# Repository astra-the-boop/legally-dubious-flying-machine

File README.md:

# la legally dubious flying machine
### Might break several aerospace, telecom, and public order laws but we ball
## Project members: Astra (@astra.celestine on Slack), Ghost (@Minh Anh Ghost on Slack), MD (not in hc), Doggy (not in hc), bingle

## Basically, an RC plane based around just regular commercial airplanes.; ~1m in length; Arduino-controlled; Using LoRa for communication; might add autopilot; DIY Controller + software

---
## Dependencies and libraries or whatever:
-

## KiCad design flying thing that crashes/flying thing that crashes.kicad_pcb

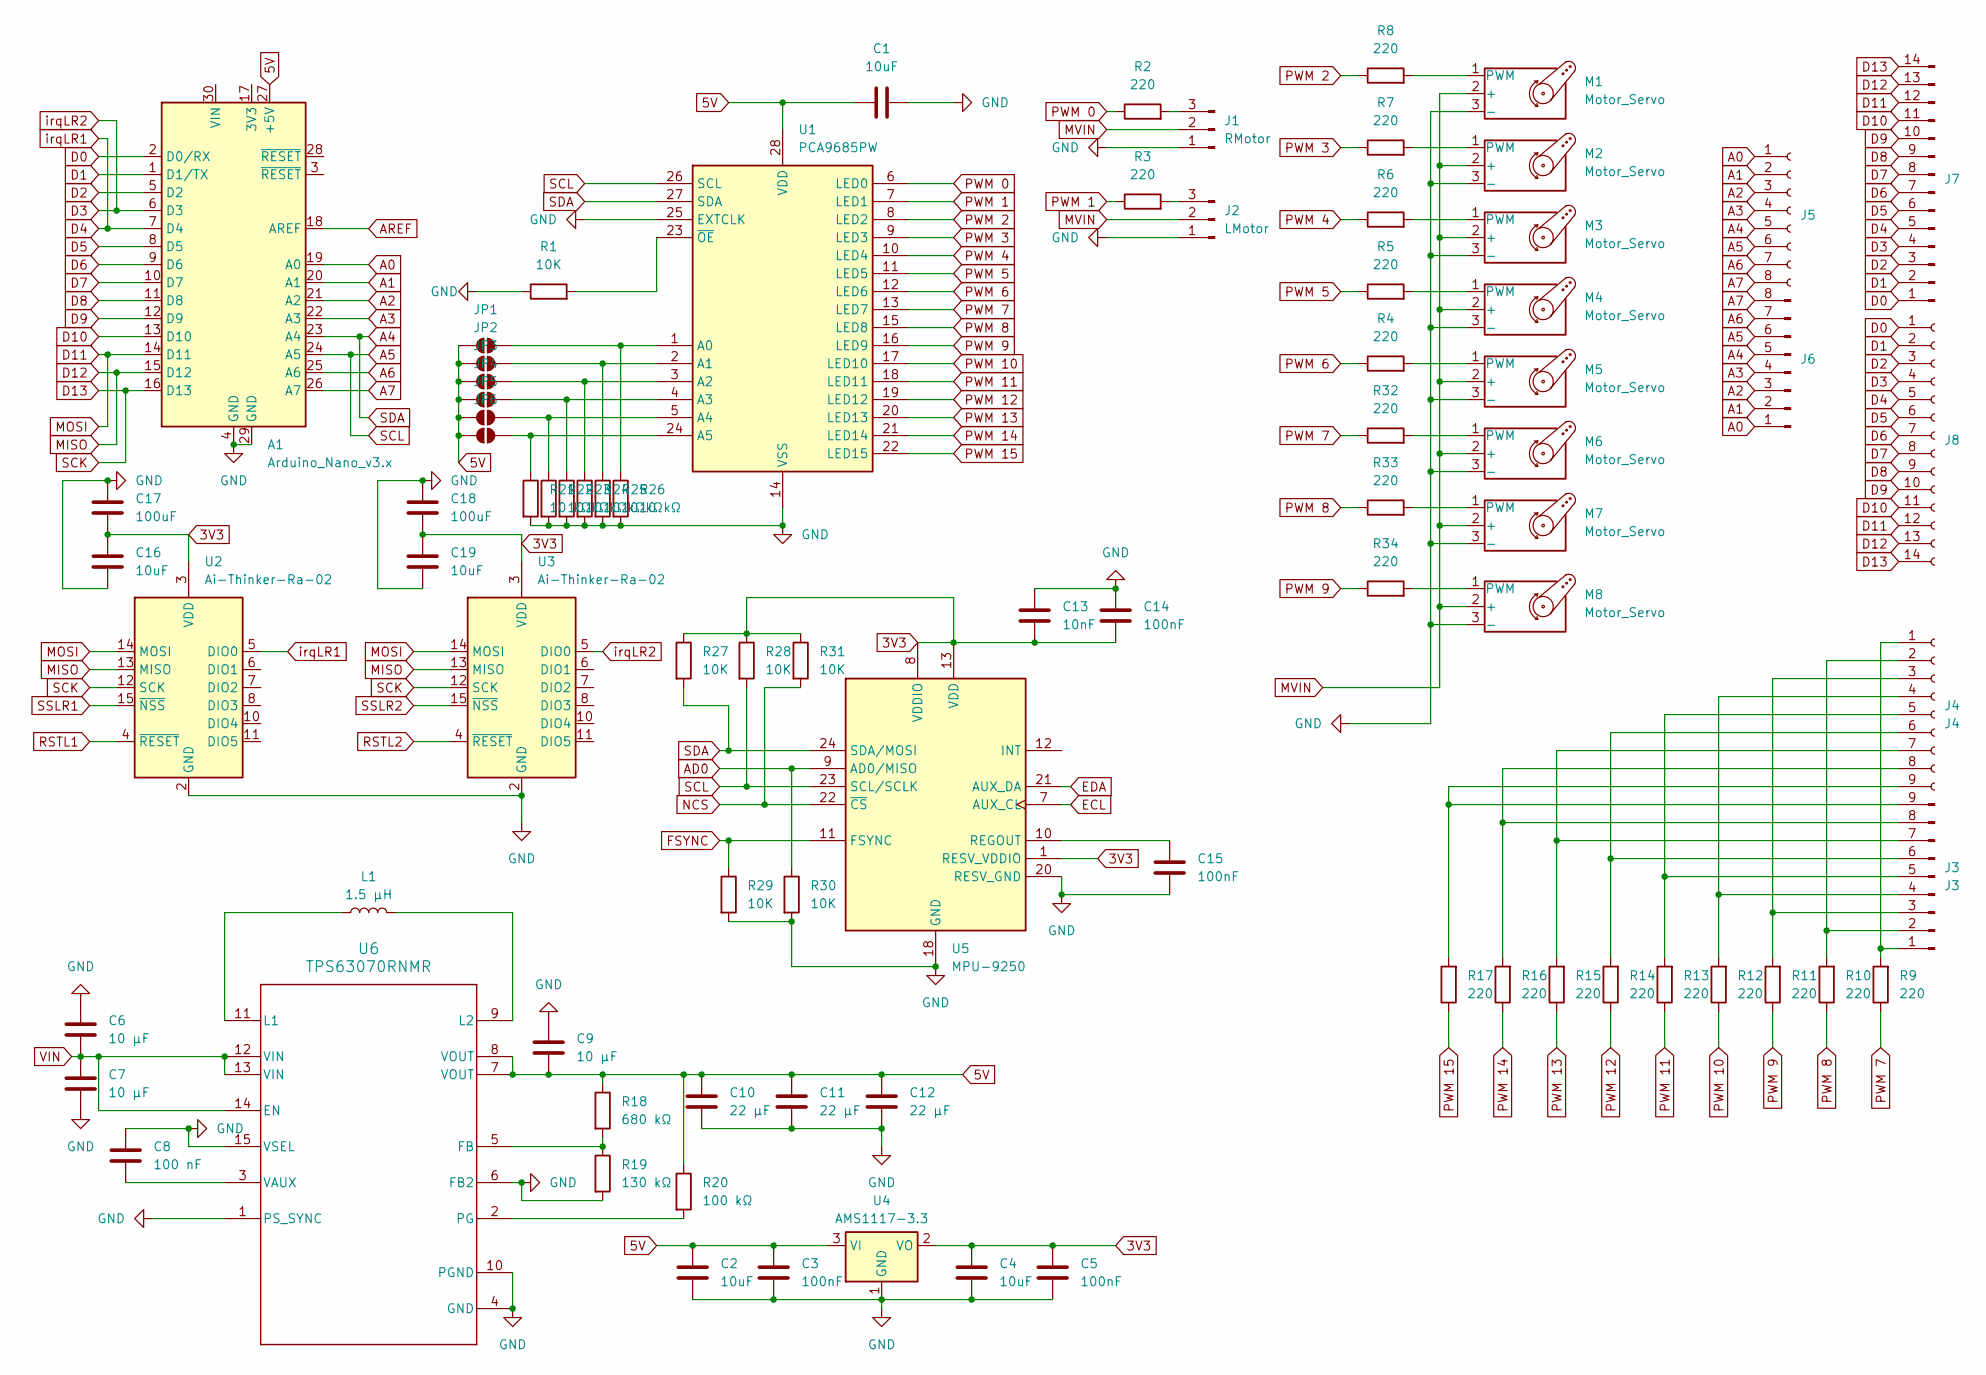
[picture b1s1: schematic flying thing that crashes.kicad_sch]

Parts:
A1: Arduino_Nano_v3.x; Arduino_Nano
C1, C2, C4: 10uF; C_0603_1608Metric
C3, C5: 100nF; C_1206_3216Metric
C6, C7: 10 µF; C_0805_2012Metric
C8: 100 nF; C_1206_3216Metric
C9: 10 µF; C_0603_1608Metric
C10, C11, C12: 22 µF; C_0805_2012Metric
C13: 10nF; C_0805_2012Metric
C14, C15: 100nF; C_0805_2012Metric
C16, C19: 10uF; C_0805_2012Metric
C17, C18: 100uF; C_0805_2012Metric
J1: RMotor; PinHeader_1x03_P2.00mm_Vertical
J2: LMotor; PinHeader_1x03_P2.00mm_Vertical
J3: J3; PinHeader_1x09_P2.00mm_Vertical
J4: J4; PinSocket_1x09_P2.00mm_Vertical
J5: PinSocket_1x08_P2.00mm_Vertical
J6: PinHeader_1x08_P2.00mm_Vertical
J7: PinHeader_1x14_P2.00mm_Vertical
J8: PinSocket_1x14_P2.00mm_Vertical
JP1, JP2, JP3, JP4, JP5, JP6: SolderJumper-2_P1.3mm_Open_RoundedPad1.0x1.5mm
L1: 1.5 µH; IND_XFL4020-152MEC
M1, M2, M3, M4, M5, M6, M7, M8: Motor_Servo; PinHeader_1x03_P2.00mm_Vertical
R1: 10K; R_1206_3216Metric
R2, R3, R4, R5, R6, R7, R8, R9, R10, R11, R12, R13, R14, R15, R16, R17, R32, R33, R34: 220; R_1206_3216Metric
R18: 680 kΩ; R_0805_2012Metric
R19: 130 kΩ; R_0805_2012Metric
R20: 100 kΩ; R_0805_2012Metric
R21, R22, R23, R24, R25, R26: 10 kΩ; R_0805_2012Metric
R27, R28, R29, R30, R31: 10K; R_0805_2012Metric
U1: PCA9685PW; TSSOP-28_4.4x9.7mm_P0.65mm
U2, U3: Ai-Thinker-Ra-02; Ai-Thinker-Ra-01-LoRa
U4: AMS1117-3.3; SOT-223-3_TabPin2
U5: MPU-9250; InvenSense_QFN-24_3x3mm_P0.4mm
U6: TPS63070RNMR; RNM0015A

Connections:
3V3: C4.1, C5.1, C13.2, C14.2, C16.1, C17.2, C18.2, C19.1, R27.1, R28.1, R31.1, U2.3 (VDD), U3.3 (VDD), U4.2 (VO), U5.1 (RESV_VDDIO), U5.8 (VDDIO), U5.13 (VDD)
5V: A1.27 (+5V), C1.1, C2.1, C3.1, C9.2, C10.1, C11.1, C12.1, JP1.1 (A), JP2.1 (A), JP3.1 (A), JP4.1 (A), JP5.1 (A), JP6.1 (A), R18.1, R20.1, U1.28 (VDD), U4.3 (VI), U6.7 (VOUT), U6.8 (VOUT)
A0: A1.19 (A0), J5.1, J6.1
A1: A1.20 (A1), J5.2, J6.2
A2: A1.21 (A2), J5.3, J6.3
A3: A1.22 (A3), J5.4, J6.4
A4: A1.23 (A4), J5.5, J6.5, R27.2, U1.27 (SDA), U5.24 (SDA/MOSI)
A5: A1.24 (A5), J5.6, J6.6, R28.2, U1.26 (SCL), U5.23 (SCL/SCLK)
A6: A1.25 (A6), J5.7, J6.7
A7: A1.26 (A7), J5.8, J6.8
AD0: R30.1, U5.9 (AD0/MISO)
AREF: A1.18 (AREF)
D0: A1.2 (D0/RX), J7.1, J8.1
D1: A1.1 (D1/TX), J7.2, J8.2
D2: A1.5 (D2), J7.3, J8.3
D3: A1.6 (D3), J7.4, J8.4, U3.5 (DIO0)
D4: A1.7 (D4), J7.5, J8.5, U2.5 (DIO0)
D5: A1.8 (D5), J7.6, J8.6
D6: A1.9 (D6), J7.7, J8.7
D7: A1.10 (D7), J7.8, J8.8
D8: A1.11 (D8), J7.9, J8.9
D9: A1.12 (D9), J7.10, J8.10
D10: A1.13 (D10), J7.11, J8.11
D11: A1.14 (D11), J7.12, J8.12, U2.14 (MOSI), U3.14 (MOSI)
D12: A1.15 (D12), J7.13, J8.13, U2.13 (MISO), U3.13 (MISO)
D13: A1.16 (D13), J7.14, J8.14, U2.12 (SCK), U3.12 (SCK)
ECL: U5.7 (AUX_CL)
EDA: U5.21 (AUX_DA)
FSYNC: R29.1, U5.11 (FSYNC)
GND: A1.4 (GND), A1.29 (GND), C1.2, C2.2, C3.2, C4.2, C5.2, C6.1, C7.2, C8.1, C9.1, C10.2, C11.2, C12.2, C13.1, C14.1, C15.2, C16.2, C17.1, C18.1, C19.2, J1.1, J2.1, M1.3 (-), M2.3 (-), M3.3 (-), M4.3 (-), M5.3 (-), M6.3 (-), M7.3 (-), M8.3 (-), R1.1, R19.2, R21.2, R22.2, R23.2, R24.2, R25.2, R26.2, R29.2, R30.2, U1.14 (VSS), U1.25 (EXTCLK), U2.1 (GND), U2.2 (GND), U2.9 (GND), U2.16 (GND), U3.1 (GND), U3.2 (GND), U3.9 (GND), U3.16 (GND), U4.1 (GND), U5.18 (GND), U5.20 (RESV_GND), U6.1 (PS_SYNC), U6.4 (GND), U6.6 (FB2), U6.10 (PGND), U6.15 (VSEL)
MVIN: J1.2, J2.2, M1.2 (+), M2.2 (+), M3.2 (+), M4.2 (+), M5.2 (+), M6.2 (+), M7.2 (+), M8.2 (+)
NCS: R31.2, U5.22 (~CS)
unnamed: J1.3, R2.2
unnamed: J2.3, R3.2
unnamed: J3.1, J4.1, R9.2
unnamed: J3.2, J4.2, R10.2
unnamed: J3.3, J4.3, R11.2
unnamed: J3.4, J4.4, R12.2
unnamed: J3.5, J4.5, R13.2
unnamed: J3.6, J4.6, R14.2
unnamed: J3.7, J4.7, R15.2
unnamed: J3.8, J4.8, R16.2
unnamed: J3.9, J4.9, R17.2
unnamed: JP1.2 (B), R26.1, U1.1 (A0)
unnamed: JP2.2 (B), R25.1, U1.2 (A1)
unnamed: JP3.2 (B), R24.1, U1.3 (A2)
unnamed: JP4.2 (B), R23.1, U1.4 (A3)
unnamed: JP5.2 (B), R22.1, U1.5 (A4)
unnamed: JP6.2 (B), R21.1, U1.24 (A5)
unnamed: M1.1 (PWM), R8.2
unnamed: M2.1 (PWM), R7.2
unnamed: M3.1 (PWM), R6.2
unnamed: M4.1 (PWM), R5.2
unnamed: M5.1 (PWM), R4.2
unnamed: M6.1 (PWM), R32.2
unnamed: M7.1 (PWM), R33.2
unnamed: M8.1 (PWM), R34.2
unnamed: R1.2, U1.23 (~OE)
unnamed: C15.1, U5.10 (REGOUT)
unnamed: R18.2, R19.1, U6.5 (FB)
unnamed: L1.1, U6.11 (L1)
unnamed: L1.2, U6.9 (L2)
unnamed: R20.2, U6.2 (PG)
unnamed: C8.2, U6.3 (VAUX)
PWM 0: R2.1, U1.6 (LED0)
PWM 1: R3.1, U1.7 (LED1)
PWM 2: R8.1, U1.8 (LED2)
PWM 3: R7.1, U1.9 (LED3)
PWM 4: R6.1, U1.10 (LED4)
PWM 5: R5.1, U1.11 (LED5)
PWM 6: R4.1, U1.12 (LED6)
PWM 7: R9.1, R32.1, U1.13 (LED7)
PWM 8: R10.1, R33.1, U1.15 (LED8)
PWM 9: R11.1, R34.1, U1.16 (LED9)
PWM 10: R12.1, U1.17 (LED10)
PWM 11: R13.1, U1.18 (LED11)
PWM 12: R14.1, U1.19 (LED12)
PWM 13: R15.1, U1.20 (LED13)
PWM 14: R16.1, U1.21 (LED14)
PWM 15: R17.1, U1.22 (LED15)
RSTL1: U2.4 (~RESET)
RSTL2: U3.4 (~RESET)
SSLR1: U2.15 (~NSS)
SSLR2: U3.15 (~NSS)
VIN: C6.2, C7.1, U6.12 (VIN), U6.13 (VIN), U6.14 (EN)

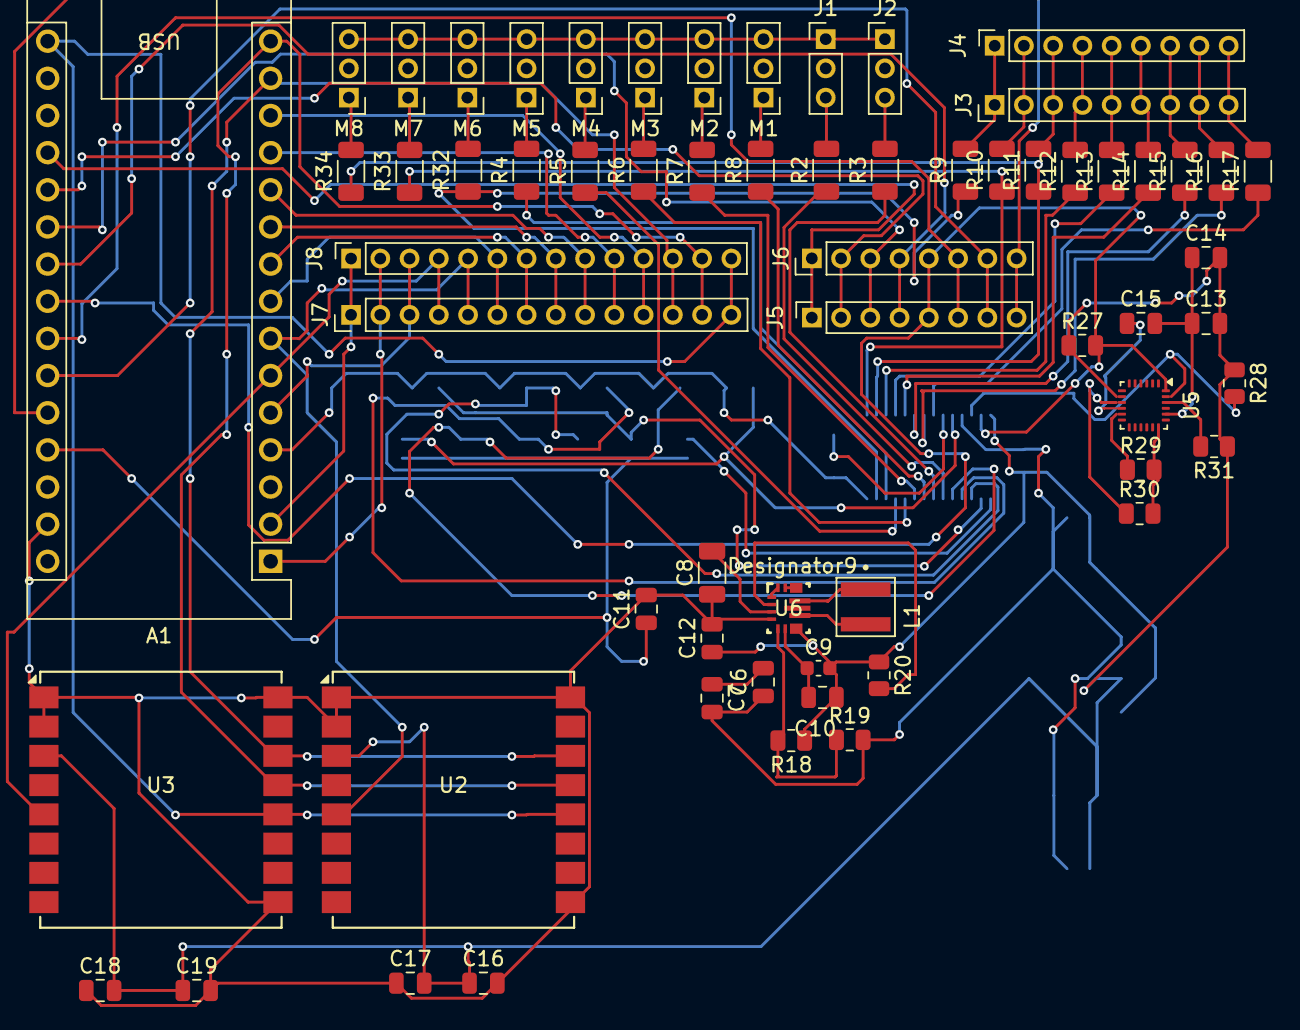
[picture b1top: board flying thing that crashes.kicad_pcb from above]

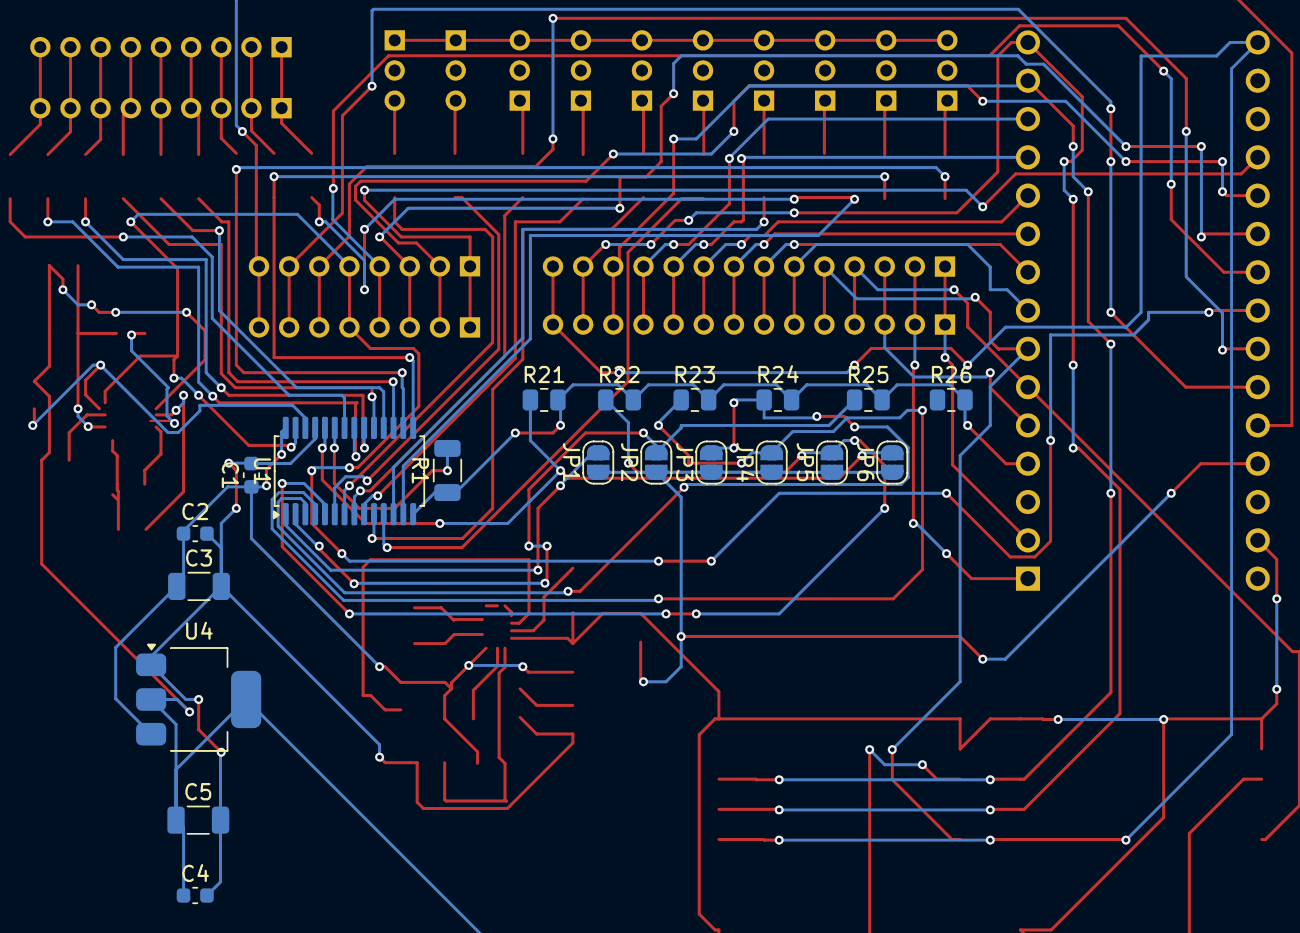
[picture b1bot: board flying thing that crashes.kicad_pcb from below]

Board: 2 copper layers, 83 parts (20 on the bottom side), 78 nets.

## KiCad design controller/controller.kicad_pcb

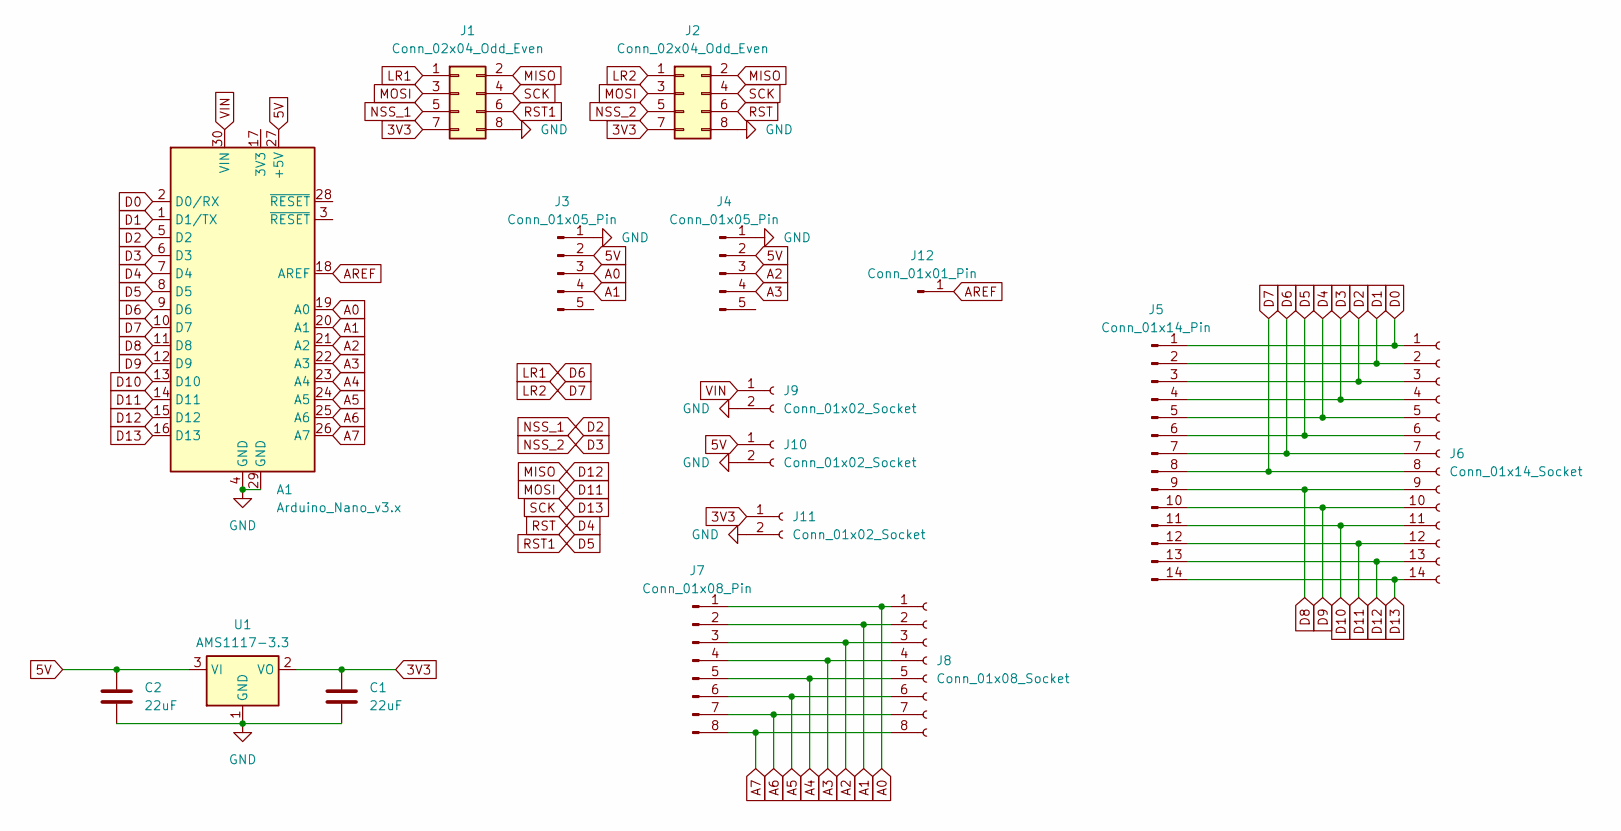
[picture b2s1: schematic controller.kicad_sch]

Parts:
A1: Arduino_Nano_v3.x; Arduino_Nano
C1, C2: 22uF; C_0603_1608Metric
J1, J2: Conn_02x04_Odd_Even; PinSocket_2x04_P2.54mm_Vertical
J3, J4: Conn_01x05_Pin; PinHeader_1x05_P2.54mm_Vertical
J5: Conn_01x14_Pin; PinHeader_1x14_P2.54mm_Vertical
J6: Conn_01x14_Socket; PinSocket_1x14_P2.54mm_Vertical
J7: Conn_01x08_Pin; PinHeader_1x08_P2.54mm_Vertical
J8: Conn_01x08_Socket; PinSocket_1x08_P2.54mm_Vertical
J9, J10, J11: Conn_01x02_Socket; PinHeader_1x02_P2.54mm_Vertical
J12: Conn_01x01_Pin; PinHeader_1x01_P2.54mm_Vertical
U1: AMS1117-3.3; SOT-223-3_TabPin2

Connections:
3V3: C1.1, J1.7, J2.7, J11.1, U1.2 (VO)
5V: A1.27 (+5V), C2.1, J3.2, J4.2, J10.1, U1.3 (VI)
A0: A1.19 (A0), J3.3, J7.1, J8.1
A1: A1.20 (A1), J3.4, J7.2, J8.2
A2: A1.21 (A2), J4.3, J7.3, J8.3
A3: A1.22 (A3), J4.4, J7.4, J8.4
A4: A1.23 (A4), J7.5, J8.5
A5: A1.24 (A5), J7.6, J8.6
A6: A1.25 (A6), J7.7, J8.7
A7: A1.26 (A7), J7.8, J8.8
AREF: A1.18 (AREF), J12.1
D0: A1.2 (D0/RX), J5.1, J6.1
D1: A1.1 (D1/TX), J5.2, J6.2
D2: A1.5 (D2), J1.5, J5.3, J6.3
D3: A1.6 (D3), J2.5, J5.4, J6.4
D4: A1.7 (D4), J2.6, J5.5, J6.5
D5: A1.8 (D5), J1.6, J5.6, J6.6
D6: A1.9 (D6), J1.1, J5.7, J6.7
D7: A1.10 (D7), J2.1, J5.8, J6.8
D8: A1.11 (D8), J5.9, J6.9
D9: A1.12 (D9), J5.10, J6.10
D10: A1.13 (D10), J5.11, J6.11
D11: A1.14 (D11), J1.3, J2.3, J5.12, J6.12
D12: A1.15 (D12), J1.2, J2.2, J5.13, J6.13
D13: A1.16 (D13), J1.4, J2.4, J5.14, J6.14
GND: A1.4 (GND), A1.29 (GND), C1.2, C2.2, J1.8, J2.8, J3.1, J4.1, J9.2, J10.2, J11.2, U1.1 (GND)
VIN: A1.30 (VIN), J9.1

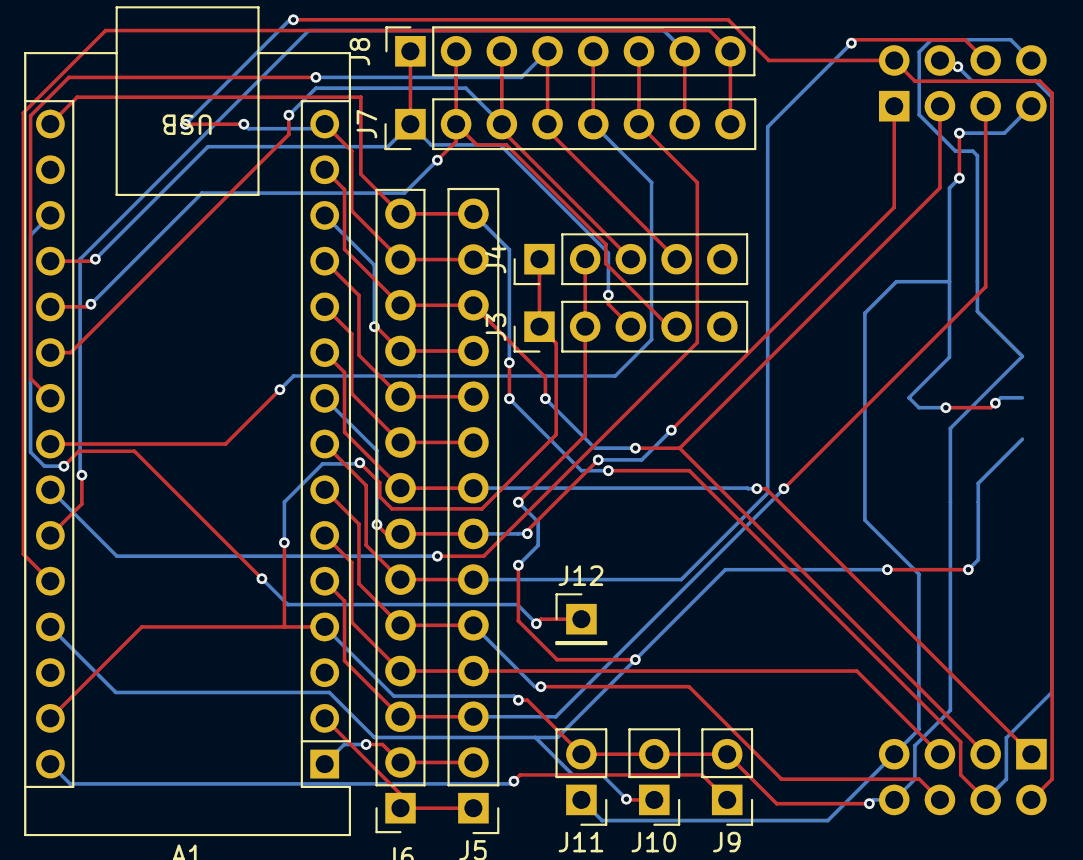
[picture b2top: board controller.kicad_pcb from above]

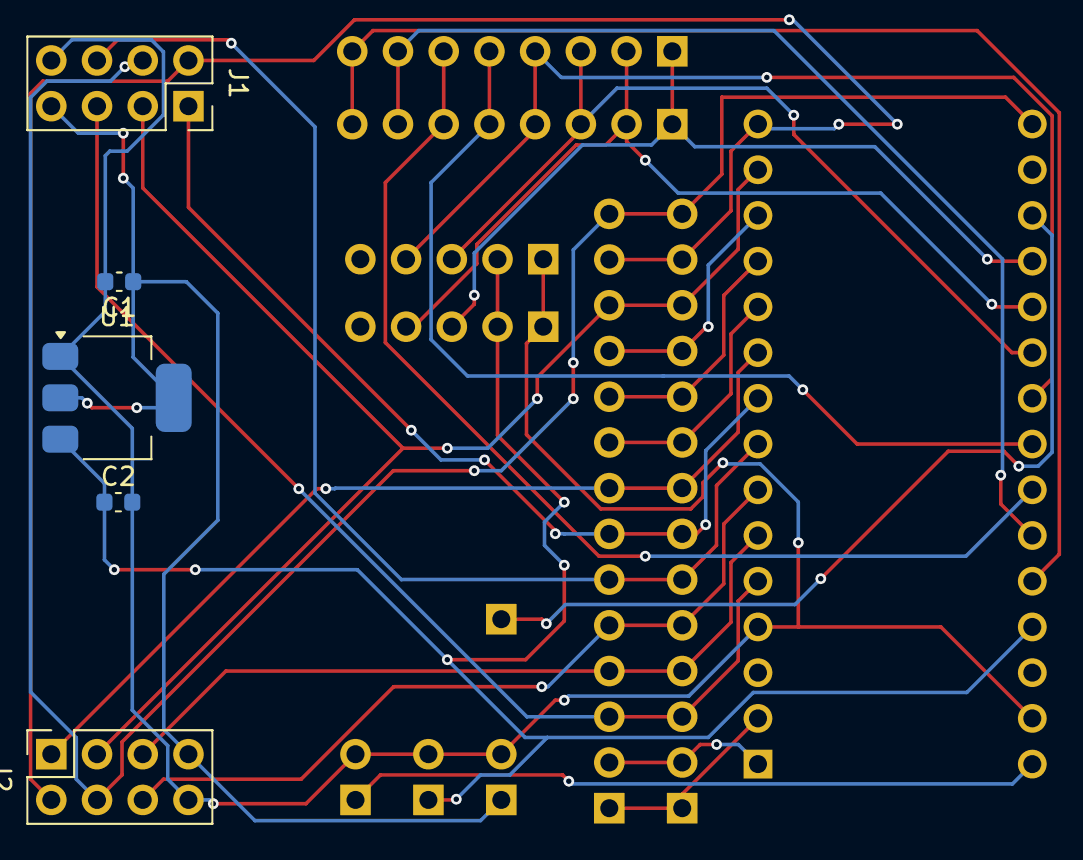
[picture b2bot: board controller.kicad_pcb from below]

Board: 2 copper layers, 16 parts (5 on the bottom side), 27 nets.

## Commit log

2025-05-17 added journal
2025-05-17 readme
2025-05-18 added group members
2025-05-25 journal 24may
2025-05-25 fix image
2025-05-25 add more media
2025-05-25 Track .MOV files with Git LFS
2025-05-25 skdaf
2025-05-25 fuck git file size limit
2025-05-25 vid fix
2025-06-06 kaboom
2025-06-09 log message
2025-06-21 jounrla
2025-06-21 jerournal
2025-07-18 Flight controller kicad design
    Flight controller plan (schematic is finished, still working on the final pcb design
2025-07-19 journal
2025-07-21 update(almost done)
2025-07-22 final draft
2025-07-22 tweeks to final draft(cleenup)
2025-07-24 controller
